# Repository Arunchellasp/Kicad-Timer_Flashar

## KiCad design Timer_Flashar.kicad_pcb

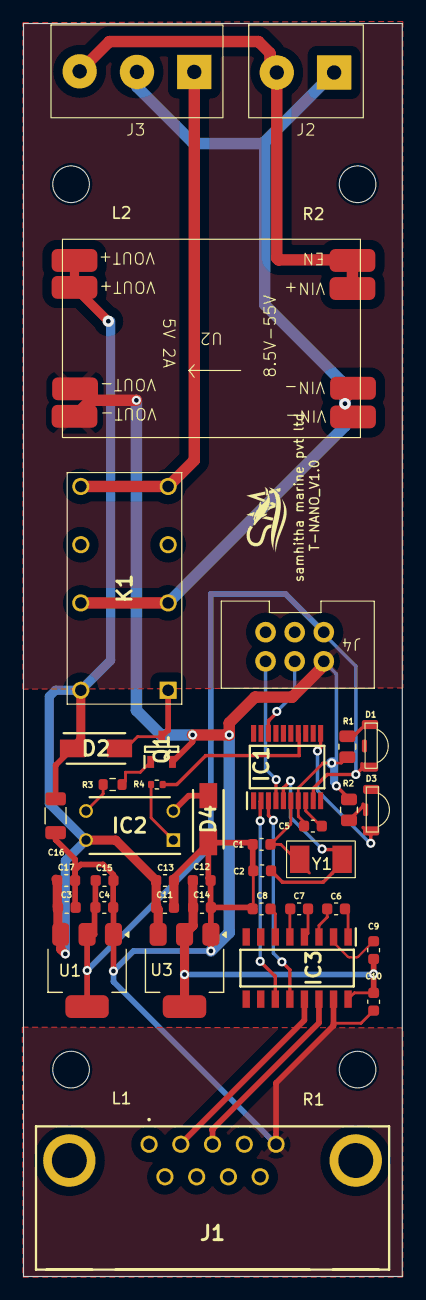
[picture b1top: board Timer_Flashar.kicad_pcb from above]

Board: 2 copper layers, 33.0 x 109.3 mm, 42 parts (0 on the bottom side), 31 nets.

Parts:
C1, C2: 22pf; C_0603_1608Metric
C3, C4, C11, C12: 0.1uF; C_0603_1608Metric
C5, C6, C7, C8, C9, C10: 1uF; C_0603_1608Metric
C13, C14, C15, C17: 10uF; C_0603_1608Metric
C16: 22uF; C_1206_3216Metric
D1, D3: INDI_LED
D2, D4: 1N4007
IC1: STM8S103F3P6; SOP65P640X120-20N
IC2: PC817X1NSZ1B; DIP762W60P254L460H455Q4N
IC3: MAX232CSE+T; SOIC127P600X175-16N
J1: L717SDE09PA4CH4F2
J2: 2 Pin Screw Terminal- 5mm Pitch
J3: 3 Pin Screw Terminal- 5mm Pitch
J4: 6 Pin Male FRC
K1: HFD27_005-S; HFD27005S
L1, L2: MountingHole_3.2mm_M3
Q1: PMBT3904,215; SOT95P230X110-3N
R1, R2: MountingHole_3.2mm_M3
R1#2, R2#2: 1k; R_0805_2012Metric
R3: 220 ohm; R_0603_1608Metric
R4: 100 ohm; R_0402_1005Metric
U1, U3: AMS1117-3.3; SOT-223-3_TabPin2
U2: 55V-5V DC-DC
Y1: 8Mhz; YSX530GA_8MHZ

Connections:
/ANODE: IC2.1 (ANODE), R4.2
/C1+: C6.2, IC3.1 (C1+)
/C1-: C6.1, IC3.3 (C1-)
/C2+: C7.2, IC3.4 (C2+)
/C2-: C7.1, IC3.5 (C2-)
/CATHODE: D4.2 (A), IC2.2 (CATHODE)
/COIL_1: D2.2 (A), K1.1 (COIL_1), Q1.3 (C)
/EMITTER: IC2.3 (EMITTER), R3.1
/NO_1: J3.3, K1.8 (NO_1), K1.9 (NO_2)
/NRST: IC1.4 (NRST), J4.6
/PA1/_OSCIN: C2.1, IC1.5 (PA1/_OSCIN), Y1.1
/PA2/_OSCOUT: C1.1, IC1.6 (PA2/_OSCOUT), Y1.2
/PB5/_I2C__SDA_[TIM1__BKIN]: D3.1, IC1.11 (PB5/_I2C__SDA_[TIM1__BKIN])
/PC4/_CLK_CCO/_TIM1__CH4/AIN2/[_TIM1__CH2N]: IC1.14 (PC4/_CLK_CCO/_TIM1__CH4/AIN2/[_TIM1__CH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), R4.1
/PD1/_SWIM: IC1.18 (PD1/_SWIM), J4.4
/R1IN: IC3.13 (R1IN), J1.2
/R1OUT: IC1.3 (PD6/_AIN6/_UART1__RX), IC3.12 (R1OUT)
/T1IN: IC1.2 (PD5/_AIN5/_UART1__TX), IC3.11 (T1IN)
/T1OUT: IC3.14 (T1OUT), J1.3
/V+: C9.1, IC3.2 (V+)
/V-: C8.2, IC3.6 (V-)
/VCAP: C5.2, IC1.8 (VCAP)
/VIN+: J2.1, J3.1, U2.3 (VIN+), U2.4 (EN)
/VIN-: J2.2, J3.2, K1.4 (COM_1), K1.13 (COM_2), U2.1 (VIN-), U2.2 (VIN-)
/VO-MUC: C4.2, C15.2, D1.1, IC1.9 (VDD), J4.1, U1.2 (VO)
/VO-RS232: C9.2, C10.2, C12.2, C14.2, IC3.16 (VCC), U3.2 (VO)
/VOUT+: C3.2, C11.2, C13.2, C16.2, C17.2, D2.1 (K), IC2.4 (COLLECTOR), K1.16 (COIL_2), U1.3 (VI), U2.7 (VOUT+), U2.8 (VOUT+), U3.3 (VI)
GND: C1.2, C2.2, C3.1, C4.1, C5.1, C8.1, C10.1, C11.1, C12.1, C13.1, C14.1, C15.1, C16.1, C17.1, D4.1 (K), IC1.7 (VSS), IC3.15 (GND), J1.5, J4.2, Q1.2 (E), R1#2.2, R2#2.2, U1.1 (GND), U2.5 (VOUT-), U2.6 (VOUT-), U3.1 (GND)
unnamed: D1.3, R1#2.1
unnamed: D3.2, R2#2.1
unnamed: Q1.1 (B), R3.2

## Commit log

2024-08-31 PCB Manufacturing completed
